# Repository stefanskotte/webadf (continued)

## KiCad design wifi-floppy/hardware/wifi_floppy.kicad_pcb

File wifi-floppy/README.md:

# WiFi Floppy Emulator (Amiga) — Pico 2 W

Gotek-style drive replacement that streams pre-encoded MFM tracks over
WiFi from your ADF webservice instead of reading a USB stick.

## Contents
- `hardware/schematic.svg` — full schematic (net names match the PCB)
- `hardware/wifi_floppy.kicad_pcb` — placed **and routed** 2-layer board,
  45°-only corners, B.Cu ground pour. Open directly in KiCad 7/8 and
  press `B` to refill the zone.
- `hardware/generate_pcb.py` — the generator that produced the board,
  including a DRC-lite checker (crossings, clearance ≥0.15 mm, 45° rule).
  Currently passes with 0 violations.
- `firmware/` — pico-sdk project (RP2350 / `PICO_BOARD=pimoroni_pico_plus2_w_rp2350`,
  pico-sdk >= 2.3.0 required — see "Firmware build requirements" below).

## Design
- **J1** 34-pin, Amiga internal pinout: pin 2 = /DSKCHG, pin 34 = /RDY
  (unlike PC drives where 34 is DSKCHG).
- **U2 74LVC541A** buffers all host-driven lines into the Pico
  (3.3 V part, 5 V-tolerant inputs). J1→A1..A8→GP2..GP9 are mapped in
  physical order, so the input routing is completely crossing-free.
- **Q1–Q6 BSS138** give open-drain outputs. They invert: **GPIO high =
  bus line pulled low**. Firmware and the PIO program already account
  for this (`OUT_ASSERT`).
- **Power**: 5 V from the Berg connector through D1 (SS14) into VSYS.
  Safe to co-power over USB while bench testing.
- PIO `flux_out` emits 2 µs bitcells (8 PIO cycles @ 4 MHz, clkdiv 37.5
  from 150 MHz), 750 ns read pulses; DMA restarts per revolution and
  raises a ~2 ms INDEX pulse at the wrap → exactly 300 rpm timing.
- 16-track LRU cache (~205 KB) + neighbour prefetch; a track is ~12.7 KB
  so a LAN fetch lands well inside a seek's settle time.

## Track server protocol — SUPERSEDED

**This section describes a protocol the firmware no longer speaks.** `http_fetch.c`,
which implemented `GET /tracks/<n>`, was deleted in plan 4a. The real device contract is
`GET /api/device/poll` (long-poll for desired state), `GET /api/device/image/<sha256>`
(the whole disk as a `WFMF` container, format defined in `image_loader.c`), and
`POST /api/device/status`. See `INTEGRATION.md` and
`docs/superpowers/specs/2026-08-29-device-plane-disk-change-design.md` §10 for the actual
contract. Kept below only as a historical note; do not implement against it.

```
GET /tracks/<n>        n = cyl*2 + side  (0..159)
 -> 200, body = [u32 LE bit_count][raw MFM bytes]
POST /tracks/<n>       (write-back, not implemented yet)
```
Encode server-side (ADF → Amiga MFM incl. 0x4489 syncs, odd/even split);
the firmware just plays bits. Suggested next step for the webservice.

## DSKCHG / RDY
`src/dskchg.c` re-implements FlashFloppy's Amiga-interface behaviour
(chgrst=step semantics, motor-edge drive-ID shifter, spin-up delay).
It's a from-scratch implementation of the observable behaviour, not a
code port. FlashFloppy is Keir Fraser's (https://github.com/keirf/flashfloppy,
Unlicense) and is credited in ../THIRD-PARTY-NOTICES.md.

## Firmware build requirements

- **pico-sdk >= 2.3.0.** `hardware_psram` (and this board's
  `PICO_PSRAM_CS_PIN`/`PICO_PSRAM_SIZE_BYTES` board-header support) landed in
  pico-sdk PR #2919, after the 2.2.0 release; 2.3.0 is the first tag that has
  it. `CMakeLists.txt` checks `PICO_SDK_VERSION_STRING` and fails the
  configure step with an explanation if `PICO_SDK_PATH` points at anything
  older.
- **`brew install arm-none-eabi-gcc` is not sufficient** — that formula ships
  GCC and libgcc but no newlib, so linking fails with `cannot find -lg`/`-lc`
  on the very first target. Use the official ARM GNU Toolchain instead (the
  `gcc-arm-embedded` cask, or the equivalent tarball from
  developer.arm.com/downloads/-/arm-gnu-toolchain-downloads) and make sure
  its `bin/` is on `PATH` ahead of any homebrew `arm-none-eabi-*` shims.
- **`PORTAL_AP_PASSWORD` must be set in the environment (plan 4b).** It becomes the WPA2
  PSK for the provisioning access point (see "Provisioning a board" below); CMake's
  configure step fails on purpose if it is unset or empty, because an invalid WPA2 PSK
  cannot be reported back to a console-less board at runtime. The full build command:

  ```bash
  export PATH="/Applications/ArmGNUToolchain/15.3.rel1/arm-none-eabi/bin:$PATH"
  export PORTAL_AP_PASSWORD=<your AP password>
  pnpm firmware:build
  ```

## First install

Verified on a board (RP2350 A4) on 2026-10-09: a blank install, a replug, pairing, over-the-air
updates in both directions, and a re-install over a paired board.

1. Download `wifi-floppy-install-<version>.uf2` from the newest `fw-<version>` release on
   GitHub. It is the only file you need.
2. Hold the **BOOT** button (the Raspberry Pi docs call it BOOTSEL) and plug the board into
   your computer over USB. A drive called `RP2350` appears.
3. Drag `wifi-floppy-install-<version>.uf2` onto that drive. The board writes the file,
   restarts by itself and starts the firmware. The drive disappears; this is expected.
4. Pair the board from the web app (see "Provisioning a board" below). Later firmware
   versions arrive over the air from the web app.

   If your phone has joined this board's setup network before, choose "Forget this
   network" for it first. The network keeps the same name after a re-install. The setup
   network has also been seen to reject the password when a phone re-joins it without a
   reboot. If that happens, unplug the board, plug it back in, and join again. This is a
   known open issue (HANDOFF).

The same file works on a blank board and on a board already running ours (both verified
on an RP2350 A4, 2026-10-09). A board running other firmware (MicroPython, say) is
expected to work too, but has not been tested. Re-installing it keeps the board's WiFi settings and pairing: it
never writes the top six flash sectors where those (and the server override) live.

What is in the file: the partition table, the firmware for partition A, and two blank
pages that clear stale headers. Every block uses the UF2 `absolute` family. The firmware
inside is built without the try-before-you-buy flag (`wifi_floppy_install`), because a
TBYB image would not start after a UF2 download. Over-the-air updates still use the TBYB
image. `tools/make_install_uf2.py` builds the file, and
`docs/superpowers/research/2026-10-09-uf2-drag-drop-first-install.md` explains the design.

With picotool you can still use `scripts/firmware-install-partitioned.sh`
(`pnpm firmware:install-partitioned`). It saves a full flash backup first.

## Provisioning a board (plan 4b)

**All five steps are verified on hardware:** steps 1-3 on 2026-09-10, and the whole flow
through Save, association and registration since. The re-join bench in `HANDOFF.md`
3bf (2026-10-09) is the latest run.

A board with no WiFi credentials stored in flash — or one that has just failed to associate
three times in a row — raises its own WPA2 access point named `wifi-floppy-XXXX`, where
`XXXX` is the last two octets of the board's MAC address (so several boards on a bench stay
distinguishable). To provision it:

1. **Mint a pairing code in webadf.** From the web app, generate a device pairing code for
   the board (single-use, 10-minute TTL — if it expires before step 4, generate a new one).
2. **Join `wifi-floppy-XXXX`** from your phone or laptop, using the WPA2 password baked into
   that board's firmware image at build time (`PORTAL_AP_PASSWORD`, above — whoever built
   the firmware knows it).
3. **Open any page** in a browser on that device. The board's DNS responder answers every
   query with its own address and the HTTP server redirects every path to `/`, so a phone's
   captive-portal probe should bring the config form up on its own; if it does not, browse to
   `http://192.168.4.1/` directly.
4. **Enter three fields**: your real WiFi network's SSID, its password, and the pairing code
   from step 1. Submitting does not commit anything yet — the board drops its own AP,
   attempts to associate with what you typed, and only writes the credentials to flash on
   success. Your phone will briefly lose the `wifi-floppy-XXXX` network while this happens.
5. **On success**, the board joins your real network and proceeds to register with webadf
   using the pairing code; the AP does not come back. **On failure** (wrong password, or the
   network was not found — the form distinguishes the two), the AP returns with the reason
   and the form is ready to try again; re-enter all three fields, since none are echoed back.

**Recovery without reflashing.** If webadf later reports the board's token as revoked or the
device row is deleted, the board erases its stored token and returns to step 1 automatically
— generate a fresh pairing code and repeat steps 2–5. The same is true of a rejected
(expired or already-used) pairing code: the board returns to the portal rather than retrying
the dead code forever.

## Watching the log

```bash
tio /dev/cu.usbmodem*          # brew install tio; it reconnects across reboots
```

Output looks like this — uptime in seconds.milliseconds, then which core:

```
[    0.002] c0 wifi-floppy boot: pimoroni_pico_plus2_w_rp2350
[    0.481] c1 radio up (RM2)
[    0.494] c1 portal: raising AP
[   34.117] c0 MOTOR        a=1 b=0
[   34.119] c0 SEL          a=1 b=0
[   34.226] c0 STEP         a=1 b=0
[   34.229] c0 TRACK-SERVED a=2 b=101376
[   34.431] c0 INDEX        a=3168 b=0
```

Two entry points, and the difference is load-bearing. `wf_logf()` formats with
`vsnprintf` and is for core1 and core0's loop. `wf_trace()` takes an integer event code
and two integers — no formatting, no format string — so it is legal inside the flux DMA
handler, where a flash-resident string would not be. `wf_trace` is placed in SRAM with
`__not_in_flash_func` for the same reason `dma_irq` is.

**core0 drains, core1 only produces.** core0's service loop already sleeps 1 ms per
iteration and the bit-level work is PIO and DMA, so it has the slack to write to USB;
core1's loop blocks for tens of seconds inside a long-poll and would strand every core0
trace behind it. A useful consequence: a core1 hang still gets its last line out, which
is why `cyw43_arch_init` failing logs before it spins forever.

The ring holds 63 records (~7 KB of SRAM). When it fills it **drops newest and counts
them**, then prints `-- N record(s) dropped --` once the backlog clears. It never blocks
a producer: a logger that stalls the floppy service loop to report on the floppy service
loop would be worse than no logger. `PICO_STDIO_USB_STDOUT_TIMEOUT_US` is set to 1 ms in
`CMakeLists.txt`, against an SDK default of 500 ms, so an unattended USB port cannot
stall that loop either.

UART stdio stays off and must stay off: GP0 and GP1 are INDEX and CHNG on this board, so
enabling it would drive the floppy bus.

## Pointing the board at your own server

For people who host their own copy of the web app. Needs firmware 1.13.0 or newer. Without an override the board
talks to `webadf.vercel.app` over TLS, as before. Not available in `WF_FW_DEBUG` bench builds.

Open the board's USB port in any serial terminal (it is USB CDC, so the speed does not matter):

```bash
screen /dev/cu.usbmodem*       # or: tio /dev/cu.usbmodem*
```

Commands, one line each:

```
wf server show                        show the server the board uses
wf server set https://host[:port]     use this server (TLS only; http:// is refused)
wf server tls noverify                accept any certificate, self-signed included; asks "type YES to confirm"
wf server tls verify                  check the certificate and host name again (the default)
wf server clear                       back to webadf.vercel.app
wf reboot
```

- Every change is refused while a disk is in DF0 or DF1: "server: eject the disk first -- nothing changed".
- `set` (to a different server) and `clear` erase the pairing **and** the Wi-Fi settings, then reboot at once into the
  setup network. Enter your Wi-Fi and a pairing code from the new server, as for a new board.
- `set` naming webadf.vercel.app itself (port 443, any letter case) is the same as `clear`; with nothing stored it
  answers "already the default".
- `tls` changes apply at the next boot (`wf reboot`). They need a server set first, so for a self-signed server run
  `set`, then `tls noverify`, then `wf reboot`, then pair.
- `noverify` also skips the host-name check. The board logs it at boot and on every new TLS connection.
- Firmware updates are still checked against the signing key built into the board, so a custom server can only
  offer builds signed by us. Build your own firmware and flash it over USB if you need something else.

## Honest caveats
- **What has run on real hardware** (rev A2 from 2026-09-10, rev B from 2026-10-02; details and dates in the root
  `HANDOFF.md`):
  - the setup portal, station join, TLS, pairing and registration;
  - reads and writes on a real A500 (Workbench 3.1 boots; saves reach the library, including after offline);
  - over-the-air firmware updates;
  - HD disks;
  - HFE, including long-track;
  - NFC tap to mount;
  - the OLED;
  - DF1 as a second drive;
  - PaulaNET networking over DF1 (Phase 2).
- **Still owed on the bench:** the open checklists recorded in `HANDOFF.md`, e.g. HD bench steps 4-7 (3ao), the
  weak-bit HFE titles, and the NFC display icon on glass (3bf).
- The host suites (`pnpm firmware:test`) and the CI build cover logic, not bus timing. Anything with a timing claim
  is only as good as its last bench run.
- The board files are a KiCad project; run `pnpm hw:verify` and real KiCad DRC, and check footprints against your
  parts, before ordering.

## PSRAM revision (Pimoroni Pico Plus 2 W)

U1 is now specified as a **Pimoroni Pico Plus 2 W** (RP2350B, 16MB flash,
8MB PSRAM, RM2 radio). It keeps the Pico footprint and pinout, so the PCB is
unchanged electrically - only the module value differs.

PSRAM is the disk. The image is pulled in **one bulk transfer at mount**
(`image_loader.c`) and the floppy bus is served entirely from RAM after
that - the read path contains no network call at all.

| where | size | role |
|-------|------|------|
| SRAM double buffer | ~26 KB | only DMA source for the flux PIO |
| PSRAM disk image | 2.03 MB | the whole disk, 160 x 13 KB slots |

**The route below is superseded** — the firmware fetches
`GET /api/device/image/<sha256>` (keyed by digest, not an integer id; see
`INTEGRATION.md` and disk-change spec §10), but the `WFMF` container body format
itself is current and matches `image_loader.c`:

    u32 magic 'WFMF'   u32 version=1   u32 track_count   u32 reserved
    per track: u32 bit_count, ceil(bits/8) bytes, padded to 4 bytes

RDY and CHNG stay deasserted until the whole image is in PSRAM, so a slow or
failed load looks like "no disk yet" to the Amiga rather than a drive that
stalls mid-track. A track missing from PSRAM is a fault, not a cache miss:
`track_cache_get()` returns NULL and nothing is streamed.

The loader parses the blob incrementally as TCP chunks arrive, writing
straight into PSRAM (a 2 MB image never fits in SRAM). It was tested on the
host against randomly-chunked input at real track sizes, plus malformed
input: oversized tracks and bad magic are rejected without overflowing a slot.

Notes / still to verify on hardware:

* **GP0/GP1 are the board's default UART pins** and carry INDEX and CHNG here.
  `pico_enable_stdio_uart(... 0)` is set; stdio goes out over USB. Do not
  re-enable UART stdio or it will drive the floppy bus.
* The flux DMA never reads PSRAM directly - a QMI cache miss contending with
  XIP can add latency at a 2 us bitcell. Tracks are copied PSRAM -> SRAM.
* **Antenna keepout position is still an assumption, and the PIM726 documents
  do not settle it.** A schematic carries no placement, and the "Pins and
  Dims" sheet's board illustration is not something to read a fab decision
  off. What the keepout currently claims, so it can be checked against a
  module in hand: it spans the module's full 21 mm width and the last 5.4 mm
  of its 51 mm length at the **non-USB end** - the pin 19-22 end, GP14-GP17.
  If the RM2's antenna is anywhere else, there is ground plane under it.
  Costs nothing to keep: GP14-GP17 are unused on this board, so the keepout
  is only wrong if it is in the wrong *place*, never merely expensive.
* ~~Confirm GP0-GP17 map to the same physical castellations on the RP2350B
  board as on the Pico 2 W.~~ **CONFIRMED 2026-09-09** against the PIM726
  schematic (sheet 3/3, "Output headers"). The Plus 2 W's header is the
  standard Pico header pin for pin: pin 1 = GP0 through pin 22 = GP17, with
  GND on 3/8/13/18/23. The only difference is that pins 6 and 7 are labelled
  `GP4_SDA` and `GP5_SCL` because they also feed the QW/ST connector - same
  GPIOs, alternate function. Every U1 signal this board uses lands where it
  was assumed to.
* Write-back path is still a skeleton: PSRAM now has TRK_DIRTY state and
  `psram_image_next_dirty()` for a flush walker, but nothing calls it yet.

## J1 floppy header - construction

J1 is a **male 2x17 through-hole pin header on 2.54 mm pitch** (both axes),
which is what a standard 34-way floppy ribbon with female IDC sockets on each
end plugs onto - same as a real 3.5" drive or a Gotek.

* Numbering is standard IDC dual-row: pin 1 and 2 adjacent across the rows,
  odd pins down one column, even down the other.
* All odd pins (1..33) are GND, matching the ribbon's alternating ground
  returns. Signals are on the even pins.
* Pin 1 now has a **square pad**, plus a silkscreen body outline and a
  chevron marker outside pin 1, so the red stripe end is unambiguous.
* Pads 1.7 mm with 1.0 mm drill - correct for the usual 0.64 mm square posts.

**Shrouded header is not a drop-in.** A keyed 2x17 IDC box header has a
10.16 mm body, which overhangs the FET drain pads by ~1.35 mm. To fit one,
the Q1-Q6 column must move about 2 mm east, which also pushes the input
routing channels. The plain header is what most drives use, so rev B keeps
it; polarity relies on the pin-1 markings and the cable's red stripe.

## Revision history - rev B is current

| rev | state |
|-----|-------|
| A   | fabricated, **scrap** - every layer mirrored, and four SOT-23s reflected |
| A2  | fabricated, **usable with a caveat** - correct except that the ground pour runs under the RM2 antenna |
| B   | **current**, not yet fabricated - A2 with the antenna keepout at the right end; copper, mask, drill and outline are byte-identical to A2 |

### Rev A2 errata - rev A boards are scrap

The first batch (rev A) came back from JLCPCB mirrored and cannot be used.
Two independent bugs, both now fixed and both now covered by
`hardware/verify_board.py`, which must be run before any future fab order.

**1. Gerber Y axis.** KiCad's coordinate system has Y increasing downward;
Gerber and Excellon have Y increasing upward, and KiCad negates Y when it
plots. `export_gerbers.py` wrote coordinates straight through, so every
layer was reflected. The renderer used the same Y-down convention, so the
preview looked correct and the verification compared the Gerbers against an
equally wrong-handed source - self-consistent, and self-consistently
mirrored.

**2. SOT-23 gate/source.** Q1, Q2, Q3 and Q6 were reflections of the
canonical KiCad SOT-23 land pattern - gate and source swapped - so a real
part would have had its gate on the GND pad and never switched. Only Q4 and
Q5 were right. Independent of bug 1; it would have shipped either way.

Fixing 2 moved the gate and source pads, which made Q3's gate pad overlap
Q4's source pad, so Q3 moved 0.6 mm north and its drain now jogs to J1 row
13 the way Q2 and Q5 already did. The INDEX, TRK0, RDY and CHNG gate routes
were re-run to suit.

`verify_board.py` now checks every footprint against the canonical KiCad land
pattern (rotation = fine, reflection = fail) and confirms the Gerber pads sit
at the mirrored Y of the .kicad_pcb. Regression-tested against the old broken
export: it reports 118/122 pads at un-mirrored Y and fails.

**A2 follow-up: antenna keepout was at the wrong end.** The rev A2 boards
were fabricated with the ground pour void over U1 pins 1/2/39/40 instead of
19/20/21/22 - the opposite end of the module. Cause: `export_gerbers.py`
flipped Y for pads, traces, silk, outline and drill, but not for the keepout
zone polygon, so the void mirrored away from the antenna. The pour audit
missed it because it used the same unflipped polygon on both sides of the
comparison - self-consistent again. Fixed, and `verify_board.py` now asserts
the keepout covers U1 pins 19-22 - reading copper out of the emitted `.GBL`
rather than re-deriving the void from the exporter, so the check cannot agree
with the exporter's mistake the way the last one did. Regression-tested both
ways: it fails on the rev A2 `.GBL` (25/25 sample points copper under the
antenna) and passes on the current one (0/25).

Consequence for the rev A2 boards in hand: they are electrically fine (all 27
GND pads still bond, no signal pad is affected) but there is ground plane
under the RM2 antenna and a harmless void near pins 1/2. Build one and check
signal strength before respinning - the whole-image PSRAM load means WiFi only
has to work at mount time.

### Rev B

The corrected files are **rev B** and have not been fabricated. Copper, mask,
drill and outline are byte-identical to rev A2 - `.GTL`, `.GTS`, `.GBS`, `.GKO`
and `.TXT` all unchanged - so an assembled rev A2 board remains a valid bring-up
target and nothing in the BOM changes. Two files differ: `.GBL` for the keepout,
and `.GTO`, because rev B is the first revision whose silkscreen will print.

**Rev B is marked.** The board says `WIFI FLOPPY REV B` on the silkscreen and
carries its reference designators; rev A and rev A2 have neither, so an unmarked
board is one of the older two. Which of those it is you tell from the pour void:
on A2 it sits at the USB end of U1, on B at the opposite end.

### Rev A and rev A2 have outlines but no lettering

**Corrected 2026-09-09 from a photograph of an assembled rev A2 board.** An
earlier version of this section said the silkscreen never printed at all and
blamed the fab for stripping it. That was wrong, and it was wrong in the
direction that flatters the diagnosis: I inferred it from a spec table instead
of from the board. J2's and U1's body outlines are plainly legible on a real
board, at 0.12 mm. Two separate things are true:

1. **The exporter dropped everything that was not an `fp_line`, and that is why
   there is no lettering.** All 13 reference designators, the antenna-keepout
   label and U2's pin-1 dot never reached the `.GTO` at all - silently, because
   nothing counted what it skipped. `export_gerbers.py` now renders text through
   `stroke_font.py`, a single-stroke vector font, and draws circles.
2. **Every silk feature was also below the fab's published minimum**, which is a
   real DFM violation even though it printed. JLCPCB's minimum silkscreen line
   width is 6 mil (0.1524 mm); the outlines were 0.12 mm and the J1 chevron
   0.15 mm, so all 17 features were under it. They came out this time. A layer
   that prints only because the fab was lenient is not one to ship again, so rev
   B draws silk at 0.2 mm and text at 1.0-1.5 mm.

Neither was visible to any check, which is the third time something wrong in the
fab output got there because nothing was looking at it. `verify_board.py` now
reads feature widths back out of the emitted `.GTO` and fails on anything below
the fab minimum, and `export_gerbers.py` reports any legend stroke that lands
within 0.15 mm of a pad. Designator placement was moved to suit: the FET column
is on a 3.14 mm pitch, so Q1-Q6 label to the east rather than above.

### Orienting the parts

D1 is the only part you can silently fit the wrong way round, so rev B marks
it: a body outline closed at the cathode end, drawn with a heavier bar than
the sides. **The SS14's banded end goes to that bar** - pad 1, the pad whose
trace runs the long way up the board, away from J2. Pad 2 is the anode, fed by
the +5V run that comes along the bottom edge from J2.

Pad 1 is the cathode by what KiCad's own `D_SMA` draws, not by convention: its
`F.Fab` layer puts the diode symbol's bar on the pad-1 side with the triangle
pointing at it, and its `F.SilkS` outline closes that end. The netlist agrees -
pad 1 is `VSYS`, pad 2 is `+5V`, and current runs anode to cathode. Reversed,
the board simply will not power from the floppy connector while still working
over USB, which is an annoying thing to debug.

Everything else is keyed:

| part | how you orient it |
|------|-------------------|
| J1, J2, U1 | square pad 1 (J1 also has the chevron). U1 matters - a 2x20 header footprint is symmetric, so the module fits rotated 180 degrees |
| U2 | pin-1 dot on the silkscreen |
| Q1-Q6 | no marking, and none needed: SOT-23 has two pads one side and one the other, so it cannot land rotated |
| C1, C3 | ceramic, not polarised |

**Still unconfirmed:** that the RM2's antenna is at the pin 19-22 end at all.
That is inherited from the CYW43 Pico 2 W and has never been checked against a
PIM726 in hand. `verify_board.py` enforces the assumption; it cannot validate
it. Confirm before ordering rev B, because moving the void is the only thing
rev B does.

Component orders are unaffected - every part in the Mouser order is still
correct for rev A2 and for rev B.

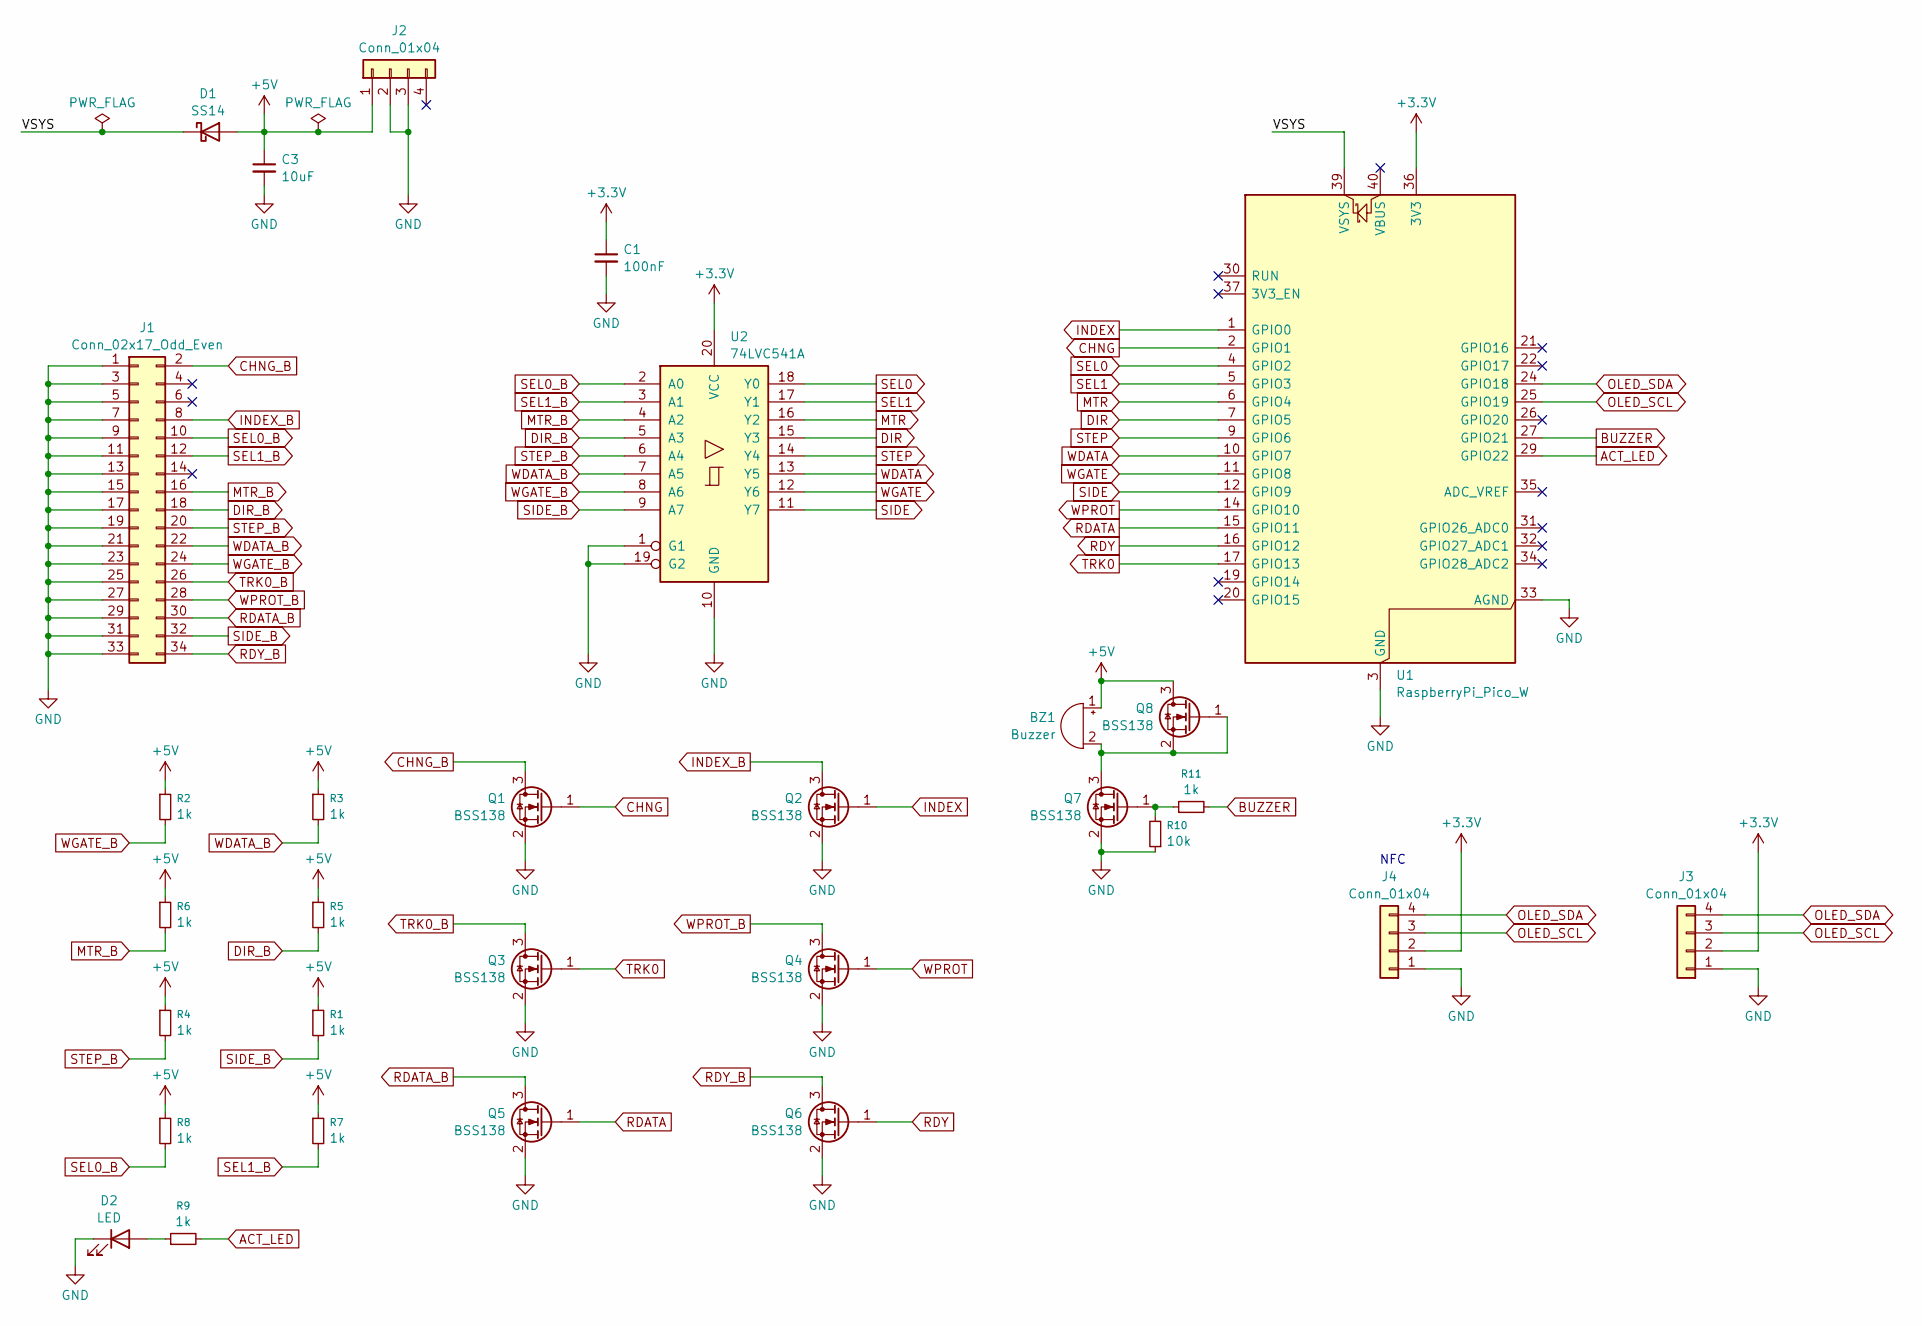
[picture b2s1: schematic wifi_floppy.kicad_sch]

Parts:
BZ1: Buzzer; Buzzer_TDK_PS1240P02BT_D12.2mm_H6.5mm; LCSC DNP
C1: 100nF; C_1206_3216Metric_Pad1.33x1.80mm_HandSolder
C3: 10uF; C_1206_3216Metric_Pad1.33x1.80mm_HandSolder
D1: SS14; D_SMA_Handsoldering
D2: LED; LED_1206_3216Metric_Pad1.42x1.75mm_HandSolder; LCSC C49018
J1: Conn_02x17_Odd_Even; IDC-Header_2x17_P2.54mm_Vertical; LCSC DNP
J2: Conn_01x04; PinHeader_1x04_P2.54mm_Horizontal; LCSC DNP
J3, J4: Conn_01x04; PinHeader_1x04_P2.54mm_Vertical; LCSC DNP
Q1, Q2, Q3, Q4, Q5, Q6, Q7, Q8: BSS138; SOT-23
R1, R2, R3, R4, R5, R6, R7, R8, R9, R11: 1k; R_1206_3216Metric_Pad1.30x1.75mm_HandSolder; LCSC C1469
R10: 10k; R_1206_3216Metric_Pad1.30x1.75mm_HandSolder; LCSC C1489
U1: RaspberryPi_Pico_W; RaspberryPi_Pico_W_SMD_HandSolder; LCSC DNP
U2: 74LVC541A; SOIC-20W_7.5x15.4mm_P1.27mm; LCSC DNP

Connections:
+3.3V: C1.1, J3.2, J4.2, U1.36 (3V3), U2.20 (VCC)
+5V: BZ1.1 (+), C3.1, D1.2 (A), J2.1, Q8.3 (D), R1.1, R2.1, R3.1, R4.1, R5.1, R6.1, R7.1, R8.1
/VSYS: D1.1 (K), U1.39 (VSYS)
ACT_LED: R9.2, U1.29 (GPIO22)
BUZZER: R11.2, U1.27 (GPIO21)
CHNG: Q1.1 (G), U1.2 (GPIO1)
CHNG_B: J1.2, Q1.3 (D)
DIR: U1.7 (GPIO5), U2.15 (Y3)
DIR_B: J1.18, R5.2, U2.5 (A3)
GND: C1.2, C3.2, D2.1 (K), J1.1, J1.3, J1.5, J1.7, J1.9, J1.11, J1.13, J1.15, J1.17, J1.19, J1.21, J1.23, J1.25, J1.27, J1.29, J1.31, J1.33, J2.2, J2.3, J3.1, J4.1, Q1.2 (S), Q2.2 (S), Q3.2 (S), Q4.2 (S), Q5.2 (S), Q6.2 (S), Q7.2 (S), R10.1, U1.3 (GND), U1.8 (GND), U1.13 (GND), U1.18 (GND), U1.23 (GND), U1.28 (GND), U1.33 (AGND), U1.38 (GND), U2.1 (G1), U2.10 (GND), U2.19 (G2)
INDEX: Q2.1 (G), U1.1 (GPIO0)
INDEX_B: J1.8, Q2.3 (D)
MTR: U1.6 (GPIO4), U2.16 (Y2)
MTR_B: J1.16, R6.2, U2.4 (A2)
unnamed: BZ1.2 (-), Q7.3 (D), Q8.1 (G), Q8.2 (S)
unnamed: D2.2 (A), R9.1
unnamed: Q7.1 (G), R10.2, R11.1
OLED_SCL: J3.3, J4.3, U1.25 (GPIO19)
OLED_SDA: J3.4, J4.4, U1.24 (GPIO18)
RDATA: Q5.1 (G), U1.15 (GPIO11)
RDATA_B: J1.30, Q5.3 (D)
RDY: Q6.1 (G), U1.16 (GPIO12)
RDY_B: J1.34, Q6.3 (D)
SEL0: U1.4 (GPIO2), U2.18 (Y0)
SEL0_B: J1.10, R8.2, U2.2 (A0)
SEL1: U1.5 (GPIO3), U2.17 (Y1)
SEL1_B: J1.12, R7.2, U2.3 (A1)
SIDE: U1.12 (GPIO9), U2.11 (Y7)
SIDE_B: J1.32, R1.2, U2.9 (A7)
STEP: U1.9 (GPIO6), U2.14 (Y4)
STEP_B: J1.20, R4.2, U2.6 (A4)
TRK0: Q3.1 (G), U1.17 (GPIO13)
TRK0_B: J1.26, Q3.3 (D)
WDATA: U1.10 (GPIO7), U2.13 (Y5)
WDATA_B: J1.22, R3.2, U2.7 (A5)
WGATE: U1.11 (GPIO8), U2.12 (Y6)
WGATE_B: J1.24, R2.2, U2.8 (A6)
WPROT: Q4.1 (G), U1.14 (GPIO10)
WPROT_B: J1.28, Q4.3 (D)

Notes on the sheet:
NFC

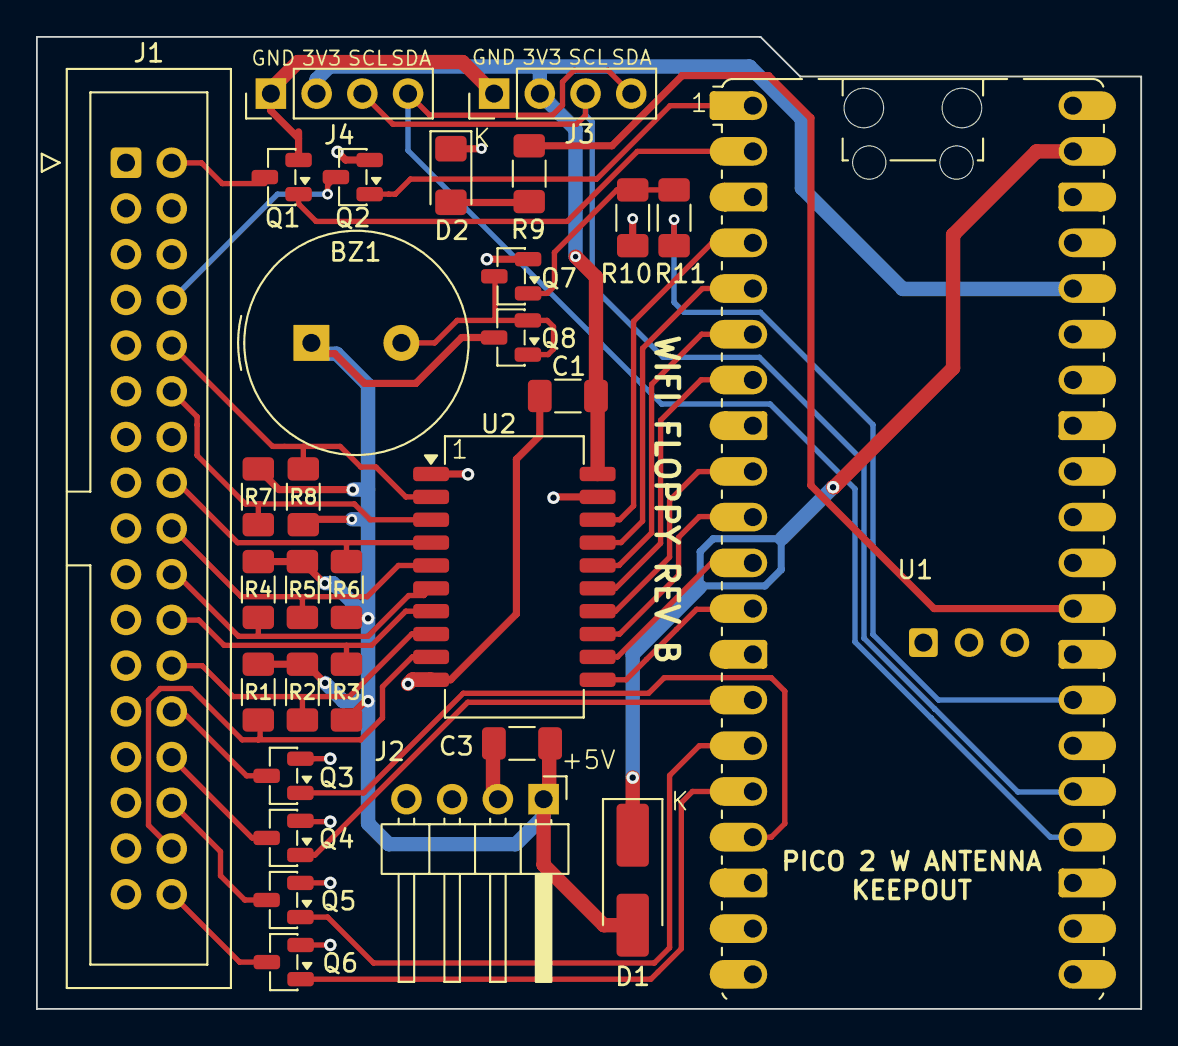
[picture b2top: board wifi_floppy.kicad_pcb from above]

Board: 2 copper layers, 61.4 x 54.0 mm, 30 parts (0 on the bottom side), 39 nets.

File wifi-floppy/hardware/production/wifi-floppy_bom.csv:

Designator,Footprint,Quantity,Value,LCSC Part #
BZ1,Buzzer_TDK_PS1240P02BT_D12.2mm_H6.5mm,1,Buzzer,DNP
C1,1206,1,100nF,
C3,1206,1,10uF,
D1,D_SMA_Handsoldering,1,SS14,
D2,1206,1,LED,C49018
J1,IDC-Header_2x17_P2.54mm_Vertical,1,Conn_02x17_Odd_Even,DNP
J2,PinHeader_1x04_P2.54mm_Horizontal,1,Conn_01x04,DNP
J3,PinHeader_1x04_P2.54mm_Vertical,1,Conn_01x04,
J4,PinHeader_1x04_P2.54mm_Vertical,1,Conn_01x04,DNP
"Q1, Q2, Q3, Q4, Q5, Q6, Q7, Q8",SOT-23,8,BSS138,
"R1, R2, R3, R4, R5",1206,5,1k,C1469
R6,1206,1,10k,C1489
U1,RaspberryPi_Pico_W_SMD_HandSolder,1,RaspberryPi_Pico_W,DNP
U2,SOIC-20W_7.5x15.4mm_P1.27mm,1,74LVC541A,DNP

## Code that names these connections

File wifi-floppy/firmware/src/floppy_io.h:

#ifndef FLOPPY_IO_H
#define FLOPPY_IO_H
// ---- pin map (matches rev A PCB) --------------------------------------
// Inputs via 74LVC541A, same polarity as bus (active-low signals read 0).
#include "board.h"
// The pin map lives in board.c (spec 2026-10-04 §5); these names stay so the
// ~60 call sites and test/run.sh's gpio_put guard read as before. They are
// runtime reads of *g_board now: never use one where C needs a constant.
#define PIN_SEL0    (g_board->sel0)
#define PIN_SEL1    (g_board->sel1)
// The select line unit d (0 = the main drive, 1 = the second) answers on: SEL0/SEL1, or, on a rev C whose
// original drive is DF0, GP3 (SEL1) for unit 0 and GP2 (SEL2 through U7) for unit 1 (orig_drive.h). board_check
// guarantees SEL1 = SEL0 + 1.
#include "orig_drive.h"
#define PIN_SEL_OF(d) (PIN_SEL0 + orig_unit_line(d))
#define PIN_MTR     (g_board->mtr)
#define PIN_DIR     (g_board->dir)      // high = step outwards (towards track 0) per Shugart DIRC
#define PIN_STEP    (g_board->step)
#define PIN_WDATA   (g_board->wdata)    // PIO capture
#define PIN_WGATE   (g_board->wgate)
#define PIN_SIDE    (g_board->side)     // low = side 1 (upper head)
// Outputs drive BSS138 gates: GPIO HIGH  ->  bus line pulled LOW (asserted).
#define PIN_WPROT   (g_board->wprot)
#define PIN_RDATA   (g_board->rdata)    // PIO side-set
#define PIN_RDY     (g_board->rdy)
#define PIN_TRK0    (g_board->trk0)
#define PIN_INDEX   (g_board->index)    // north-edge pin; GP14/15 sit in antenna keepout
#define PIN_CHNG    (g_board->chng)

#define OUT_ASSERT   1     // remember: inverted driver
#define OUT_RELEASE  0

// ---- aux pins (bring-up only, wired by hand) ---------------------------
// NOT on the PCB: these are bare, unrouted through-holes in U1's footprint,
// reachable with Dupont leads on the header pins that pass through the top.
// Chosen, and the reasoning matters if they are ever moved:
//
//   * GP14..GP17 (header pins 19-22) are the ONLY other free GPIOs and are
//     all unusable. The antenna keepout spans BOTH header rows, so the east
//     row mirrors the west: pins 21/22 land at the same y as 20/19. The
//     keepout allows pads but forbids tracks and vias, so nothing can be
//     routed to them -- and the same reason (it is the antenna end) makes
//     them a bad place to hang flying leads even when routing is not the
//     question.
//   * I2C1, not I2C0, although GP20/21 would mux correctly for I2C0. I2C0's
//     other pins are GP4/GP5 -- this board's MTR and DIR, and also where the
//     PIM726's Qw/ST connector is hardwired. A driver that ever calls
//     i2c_init(i2c0, ...) with default pins would reconfigure two live
//     floppy inputs; on I2C1 that mistake is harmless.
//   * GP22 for the LED rather than GP26/27/28, which are the only
//     ADC-capable pins left and are worth keeping for sensing the +5V/+12V
//     rails or VSYS later.
//
// THE LED IS NOT INVERTED. Every other output here drives a BSS138 gate,
// where GPIO high pulls the bus line LOW (OUT_ASSERT above). This one is a
// direct drive: high = lit. Do not reach for OUT_ASSERT.
//
// The panel must be powered from 3V3 (header pin 36), never VSYS/VBUS: most
// SSD1306 modules pull SDA/SCL up to their own VCC, and RP2350 GPIOs are not
// 5V tolerant.
// Header pin 29 -> series resistor -> LED -> GND. VERIFIED WORKING on a rev A2
// board 2026-09-12 -- but wired on the bench with NO resistor, which is out of
// spec even though it lights: see led_init(), which drops the pad to its
// weakest drive to compensate. Rev B is unfabricated; put the resistor in.
#define PIN_ACT_LED  (g_board->act_led)
#define PIN_I2C_SDA  (g_board->i2c_sda)    // header pin 24 on the PIM726, I2C1 SDA
#define PIN_I2C_SCL  (g_board->i2c_scl)    // header pin 25 on the PIM726, I2C1 SCL

#define NUM_CYL      80
#define NUM_SIDES    2
#define RPM          300
#define REV_US       200000            // 200 ms / rev
#define BITCELL_NS   2000              // Amiga DD MFM
// The DD raw MFM track-size ceiling lives in psram_image.h as
// TRACK_MAX_BYTES, not here: it has to be the same constant the PSRAM slot
// and the SRAM staging buffer are both sized against (see psram_image.h for
// why two different values here was a live overflow).
#define INDEX_PULSE_US 2000
#endif

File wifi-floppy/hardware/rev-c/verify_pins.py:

#!/usr/bin/env python3
# verify_pins.py <board>: checks rev C's connections against sources that did not build it: the RP2350 datasheet's pin
# table, the firmware's board.c, the pico-sdk board header, the RM2 datasheet's table 2 and rev B's own board.
import re, sys, json, os, pcbnew
HERE = os.path.dirname(os.path.abspath(__file__))
c = pcbnew.LoadBoard(sys.argv[1]); r = pcbnew.LoadBoard(os.path.join(HERE, '../wifi_floppy.kicad_pcb'))
bad = []; ok = 0
def check(what, got, want):
    global ok
    if got == want: ok += 1
    else: bad.append(f'{what}: board has {got!r}, source says {want!r}')
def pad(board, ref, n):
    return [p.GetNetname().split('/')[-1] for p in board.FindFootprintByReference(ref).Pads() if p.GetNumber() == str(n)]
# RP2350 datasheet tables 1427-1432, extracted from the PDF (RP-008373-DS-2)
DS = json.load(open(os.path.join(HERE, 'rp2350-qfn80-pins.json')))
gp = lambda g: DS[f'GPIO{g}'] if f'GPIO{g}' in DS else DS[[k for k in DS if k.startswith(f'GPIO{g}_')][0]]
# firmware pin map
src = open(os.path.join(HERE, '../../firmware/src/board.c')).read()
role = {m[0]: int(m[1]) for m in re.findall(r'\.(\w+) = (\d+)', src)}
want = dict(sel0='SEL0', sel1='SEL1', mtr='MTR', dir='DIR', step='STEP', wdata='WDATA', wgate='WGATE', side='SIDE', wprot='WPROT', rdata='RDATA',
            rdy='RDY', trk0='TRK0', index='INDEX', chng='CHNG', act_led='ACT_LED', i2c_sda='OLED_SDA', i2c_scl='OLED_SCL')
for k, net in want.items(): check(f'firmware {k} GP{role[k]} pin {gp(role[k])}', pad(c, 'U1', gp(role[k])), [net])
# SDK board header: radio and PSRAM
h = open(os.path.expanduser('~/pico-sdk/src/boards/include/boards/pimoroni_pico_plus2_w_rp2350.h')).read()
val = lambda name: int(re.search(rf'#define {name} (\d+)', h).group(1))
for name, net in (('CYW43_DEFAULT_PIN_WL_REG_ON','WL_ON'),('CYW43_DEFAULT_PIN_WL_DATA_OUT','WL_D'),('CYW43_DEFAULT_PIN_WL_CLOCK','WL_CLK'),
                  ('CYW43_DEFAULT_PIN_WL_CS','WL_CS'),('PIMORONI_PICO_PLUS2_W_PSRAM_CS_PIN','PSRAM_CS')):
    check(f'SDK {name}', pad(c, 'U1', gp(val(name))), [net])
# RP2350 special pins
for name, net in (('QSPI_SS','QCS'),('QSPI_SD0','QSD0'),('QSPI_SD1','QSD1'),('QSPI_SD2','QSD2'),('QSPI_SD3','QSD3'),('QSPI_SCLK','QSCLK'),
                  ('XIN','XIN'),('XOUT','XOUT_RP'),('RUN','RUN'),('SWCLK','SWCLK'),('SWDIO','SWDIO'),('USB_DP','USB_DP_RP'),('USB_DM','USB_DM_RP'),
                  ('VREG_AVDD','VREG_AVDD'),('VREG_LX','VREG_LX'),('VREG_PGND','GND'),('VREG_VIN','+3.3V'),('VREG_FB','DVDD'),('ADC_AVDD','ADC_AVDD'),
                  ('QSPI_IOVDD','+3.3V'),('USB_OTP_VDD','+3.3V')):
    check(f'RP2350 {name}', pad(c, 'U1', DS[name]), [net])
for p in (5,15,24,29,41,50,60,76): check(f'IOVDD pin {p}', pad(c, 'U1', p), ['+3.3V'])
for p in (10,32,51): check(f'DVDD pin {p}', pad(c, 'U1', p), ['DVDD'])
# RM2 datasheet table 2
RM2 = {1:'GND',3:'WL_CLK',4:'GND',5:'WL_D',7:'GND',9:'WL_CS',11:'GND',12:'WL_ON',13:'WL_ON',14:'VDDBAT',15:'GND',16:'VDDBAT',21:'GND'}
for n, net in RM2.items(): check(f'RM2 pad {n}', pad(c, 'M1', n), [net])
def two(ref, a, b):
    got = sorted(pad(c, ref, 1) + pad(c, ref, 2)); check(f'{ref} joins {a} and {b}', got, sorted([a, b]))
two('R30', 'WL_D', 'WL_DO'); two('R31', 'WL_D', 'WL_IRQ')
check('RM2 pad 6 (470 ohm to GP24)', pad(c, 'M1', 6), ['WL_DO']); check('RM2 pad 10 (10k to GP24)', pad(c, 'M1', 10), ['WL_IRQ'])
# memory pinouts (W25Q128 and PSRAM: CS SO SIO2 GND SI CLK SIO3 VCC)
for ref, cs in (('U3','QCS'),('U4','PSRAM_CS')):
    for n, net in zip(range(1, 9), (cs,'QSD1','QSD2','GND','QSD0','QSCLK','QSD3','+3.3V')): check(f'{ref} pin {n}', pad(c, ref, n), [net])
# every part kept from rev B has the same pads on the same nets
kept = 0
for f in r.Footprints():
    ref = f.GetReference()
    if ref == 'U1': continue
    for p in f.Pads():
        if p.GetNetname().startswith('unconnected'): continue   # names of no-connects follow the schematic
        if (ref, p.GetNumber()) == ('U2', '2'):                 # 2026-11-17: U2's A0 now comes from the SEL0/SEL2 mux U7
            check('U2.2 from the mux U7.4', pad(c, 'U2', 2), ['SEL0M_B']); check('mux U7 IN1 is rev B U2.2 net', pad(c, 'U7', 1), [p.GetNetname()])
            continue
        if (ref, p.GetNumber()) == ('J2', '1'):                 # 2026-11-18: power in now reaches +5V through the fuse F1
            check('J2.1 into fuse F1', pad(c, 'F1', 1), ['+5V_IN']); check('F1 out is rev B J2.1 net', pad(c, 'F1', 2), [p.GetNetname()])
            check('J2.1 is +5V_IN', pad(c, 'J2', 1), ['+5V_IN'])
            continue
        kept += 1; check(f'rev B {ref}.{p.GetNumber()}', pad(c, ref, p.GetNumber())[0] if pad(c, ref, p.GetNumber()) else None, p.GetNetname().replace('/VSYS', 'VSYS'))
print(f'{ok} checks passed ({kept} rev B pads), {len(bad)} failed')
for b in bad: print(' FAIL', b)

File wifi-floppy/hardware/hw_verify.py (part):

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        d = descr(v)
        if v['severity'] != 'error':
            warnings += 1
        elif v['type'] == 'power_pin_not_driven' and 'VSYS' in d:
            pass
        elif v['type'] == 'pin_to_pin' and 'GND' in d and 'AGND' in d:
            pass
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        got = net_of('J5', pin) or ''
        if pin == 10:
            if got != 'DRV_SEL_B':
                fail(f'J5 pin 10: net {got!r}, expected DRV_SEL_B (the gated select)')
        elif pin in (4, 6, 12, 14):
            if not got.startswith('unconnected'):
                fail(f'J5 pin {pin}: net {got!r}, expected no connection (pin 12 = SEL1 must not reach the drive)')
        elif got != net_of('J1', pin):
            fail(f'J5 pin {pin}: net {got!r}, J1 pin {pin} has {net_of("J1", pin)!r}')
    for pin in range(1, 35, 2):
        want = 'DRV_DET_B' if pin in (1, 33) else 'GND'
        if net_of('J5', pin) != want:
            fail(f'J5 pin {pin}: net {net_of("J5", pin)!r}, expected {want}')
    for net in ('DRV_SEL_B', 'SEL2_B'):
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
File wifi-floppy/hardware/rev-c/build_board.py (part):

#!/usr/bin/env python3
# Rev C routing proof: rev B with the PIM726 module replaced by its parts (Pimoroni Pico Plus 2 W schematic), the
# GPIOs unchanged. Run with KiCad's own Python. Writes rev-c.kicad_pcb, unrouted. rev B is only read.
# Usage: build_board.py <copper layers 2|4> <out.kicad_pcb>
import sys, os, pcbnew
LAYERS, OUT = int(sys.argv[1]), sys.argv[2]
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for p in f.Pads():
    if p.GetNumber() in ('', '81'): p.SetNet(net('GND'))
# decoupling around the package, as Pimoroni's sheet 1
L = lambda p: U[1]-3.8+0.4*(p-1)      # left side, y of pin p
BX = lambda p: U[0]-3.8+0.4*(p-21)    # bottom, x of pin p
RY = lambda p: U[1]+3.8-0.4*(p-41)    # right, y of pin p
TX = lambda p: U[0]+3.8-0.4*(p-61)    # top, x of pin p
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R('R21', 154.6, 116.9, '220', V33, 'ADC_AVDD')
C6('C24', 154.6, 115.4, '2.2uF', 'ADC_AVDD')
# crystal
put('Y1', 'Crystal', 'Crystal_SMD_3225-4Pin_3.2x2.5mm', 147, 132.3, 0, 'ABM8-272-T3', {'1':'XIN','2':'GND','3':'XOUT','4':'GND'})
C('C25', 143.9, 132.0, '15pF', 'XIN', rot=90)
C('C26', 150.3, 133.2, '15pF', 'XOUT', rot=90)
R('R22', 150.3, 130.6, '1k', 'XOUT', 'XOUT_RP', rot=90)
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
